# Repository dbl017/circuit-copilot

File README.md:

# CircuitCopilot

Object-aware AI engineering copilot for KiCad combining live design context, engineering documentation, deterministic EE analysis, and safe AI-assisted design workflows.

## Vision

> **CircuitCopilot is an object-aware AI engineering assistant for KiCad that combines live design context, authoritative engineering documentation, deterministic EE tools, and multimodal reasoning to help engineers understand, validate, troubleshoot, learn, and safely modify electronic designs without leaving their EDA workflow.**

The signature interaction CircuitCopilot is working toward:

```
Engineer
  -> hover/select component in KiCad
  -> CircuitCopilot automatically understands the selected object
  -> understands circuit/connectivity context
  -> retrieves authoritative documentation
  -> performs deterministic EE analysis when appropriate
  -> AI explains the result
  -> suggests an engineering action
  -> previews the change
  -> engineer approves
  -> KiCad action occurs
```

The core idea: **AI should understand what the engineer is currently working on without requiring the engineer to manually describe the entire circuit to a chatbot.**

This vision is a working hypothesis and is expected to evolve as the project is built and learned from.

## Why This Project?

General-purpose chatbots can already answer electronics questions, but they have no direct awareness of the object currently selected in an EDA tool, the design's connectivity, the project's state, component relationships, or the engineer's workflow context. CircuitCopilot explores what changes when AI is brought directly into the engineering workflow itself, instead of living in a separate chat window that has to be told everything by hand.

## Core Principles

- Object-aware: understand the design and the selected object, not just free text.
- Evidence-backed: engineering answers should cite authoritative sources.
- Engineering validation: deterministic calculations where practical, not just LLM reasoning.
- Human-in-the-loop: the engineer approves consequential design changes.
- Incremental: build and learn one capability at a time.
- Learning-oriented: understanding the system matters as much as the system working.

See [`docs/architecture/overview.md`](docs/architecture/overview.md) for the full philosophy and architectural categories.

## Current Status

**M0 — Foundations.**

This project is in very early development. No application functionality exists yet: there is no KiCad connection, no agents, no RAG, and no UI. The repository currently contains project structure, documentation, and a roadmap only. See [`progress/CURRENT.md`](progress/CURRENT.md) for the active sprint.

## Proposed Architecture

CircuitCopilot is currently exploring a multi-agent architecture (Orchestrator, Design Agent, Documentation Agent, EE Analysis Agent, Vision Agent, Tutor Agent, Component/Library Agent). **This is provisional and subject to change** — see [`docs/architecture/overview.md`](docs/architecture/overview.md) for details, and note that fewer agents, or a single agent with deterministic tools, may turn out to be the better design. That comparison is itself a planned milestone (M6).

## Roadmap

See [`ROADMAP.md`](ROADMAP.md) for the full milestone plan, from M0 (Foundations) through M10 (Advanced / Innovation Sandbox).

## Learning Project

CircuitCopilot is both an engineering project and a structured learning project. It is being built progressively, on purpose, to learn: EDA automation, KiCad APIs, Python software engineering, Git/GitHub practices, AI/RAG, agent design, multimodal AI, and engineering validation. AI coding assistants are used as pair programmers, reviewers, and instructors — not as a way to generate the whole application at once. See [`CONTRIBUTING.md`](CONTRIBUTING.md) for the AI assistant policy and [`docs/learning-log/`](docs/learning-log/README.md) for what's been learned along the way.

## Repository Structure

```
circuit-copilot/
├── README.md, ROADMAP.md, CONTRIBUTING.md, LICENSE
├── docs/            architecture, decision records, research notes, learning log
├── progress/        current sprint, milestone tracking, idea backlog
├── src/circuitcopilot/   kicad/, agents/, knowledge/, engineering/, vision/, ui/
├── tests/           engineering/, retrieval/, agents/
├── examples/        small runnable examples
├── sample-projects/ sample KiCad projects used for development
└── data/            manifests and small permitted sample data (see data/README.md)
```

## Safety / Engineering Disclaimer

CircuitCopilot is experimental engineering software and should not be relied upon for safety-critical design decisions without independent professional verification.

## License

[MIT](LICENSE)

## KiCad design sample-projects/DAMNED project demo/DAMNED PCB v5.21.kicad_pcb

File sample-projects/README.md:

# Sample Projects

This directory contains KiCad projects used to develop and evaluate CircuitCopilot.

## DAMNED

`DAMNED project demo/` is an existing, working embedded-electronics KiCad project being used as the first realistic CircuitCopilot test fixture. It predates CircuitCopilot and has been opened across more than one KiCad version, so its schematic and PCB files may report different KiCad generator versions from each other and from the currently installed KiCad release — that's expected, and is not something to "fix" by hand.

It will eventually help test:

- KiCad IPC connectivity
- board/component enumeration
- net/connectivity analysis
- component-context extraction
- engineering checks
- documentation retrieval
- object-aware assistance

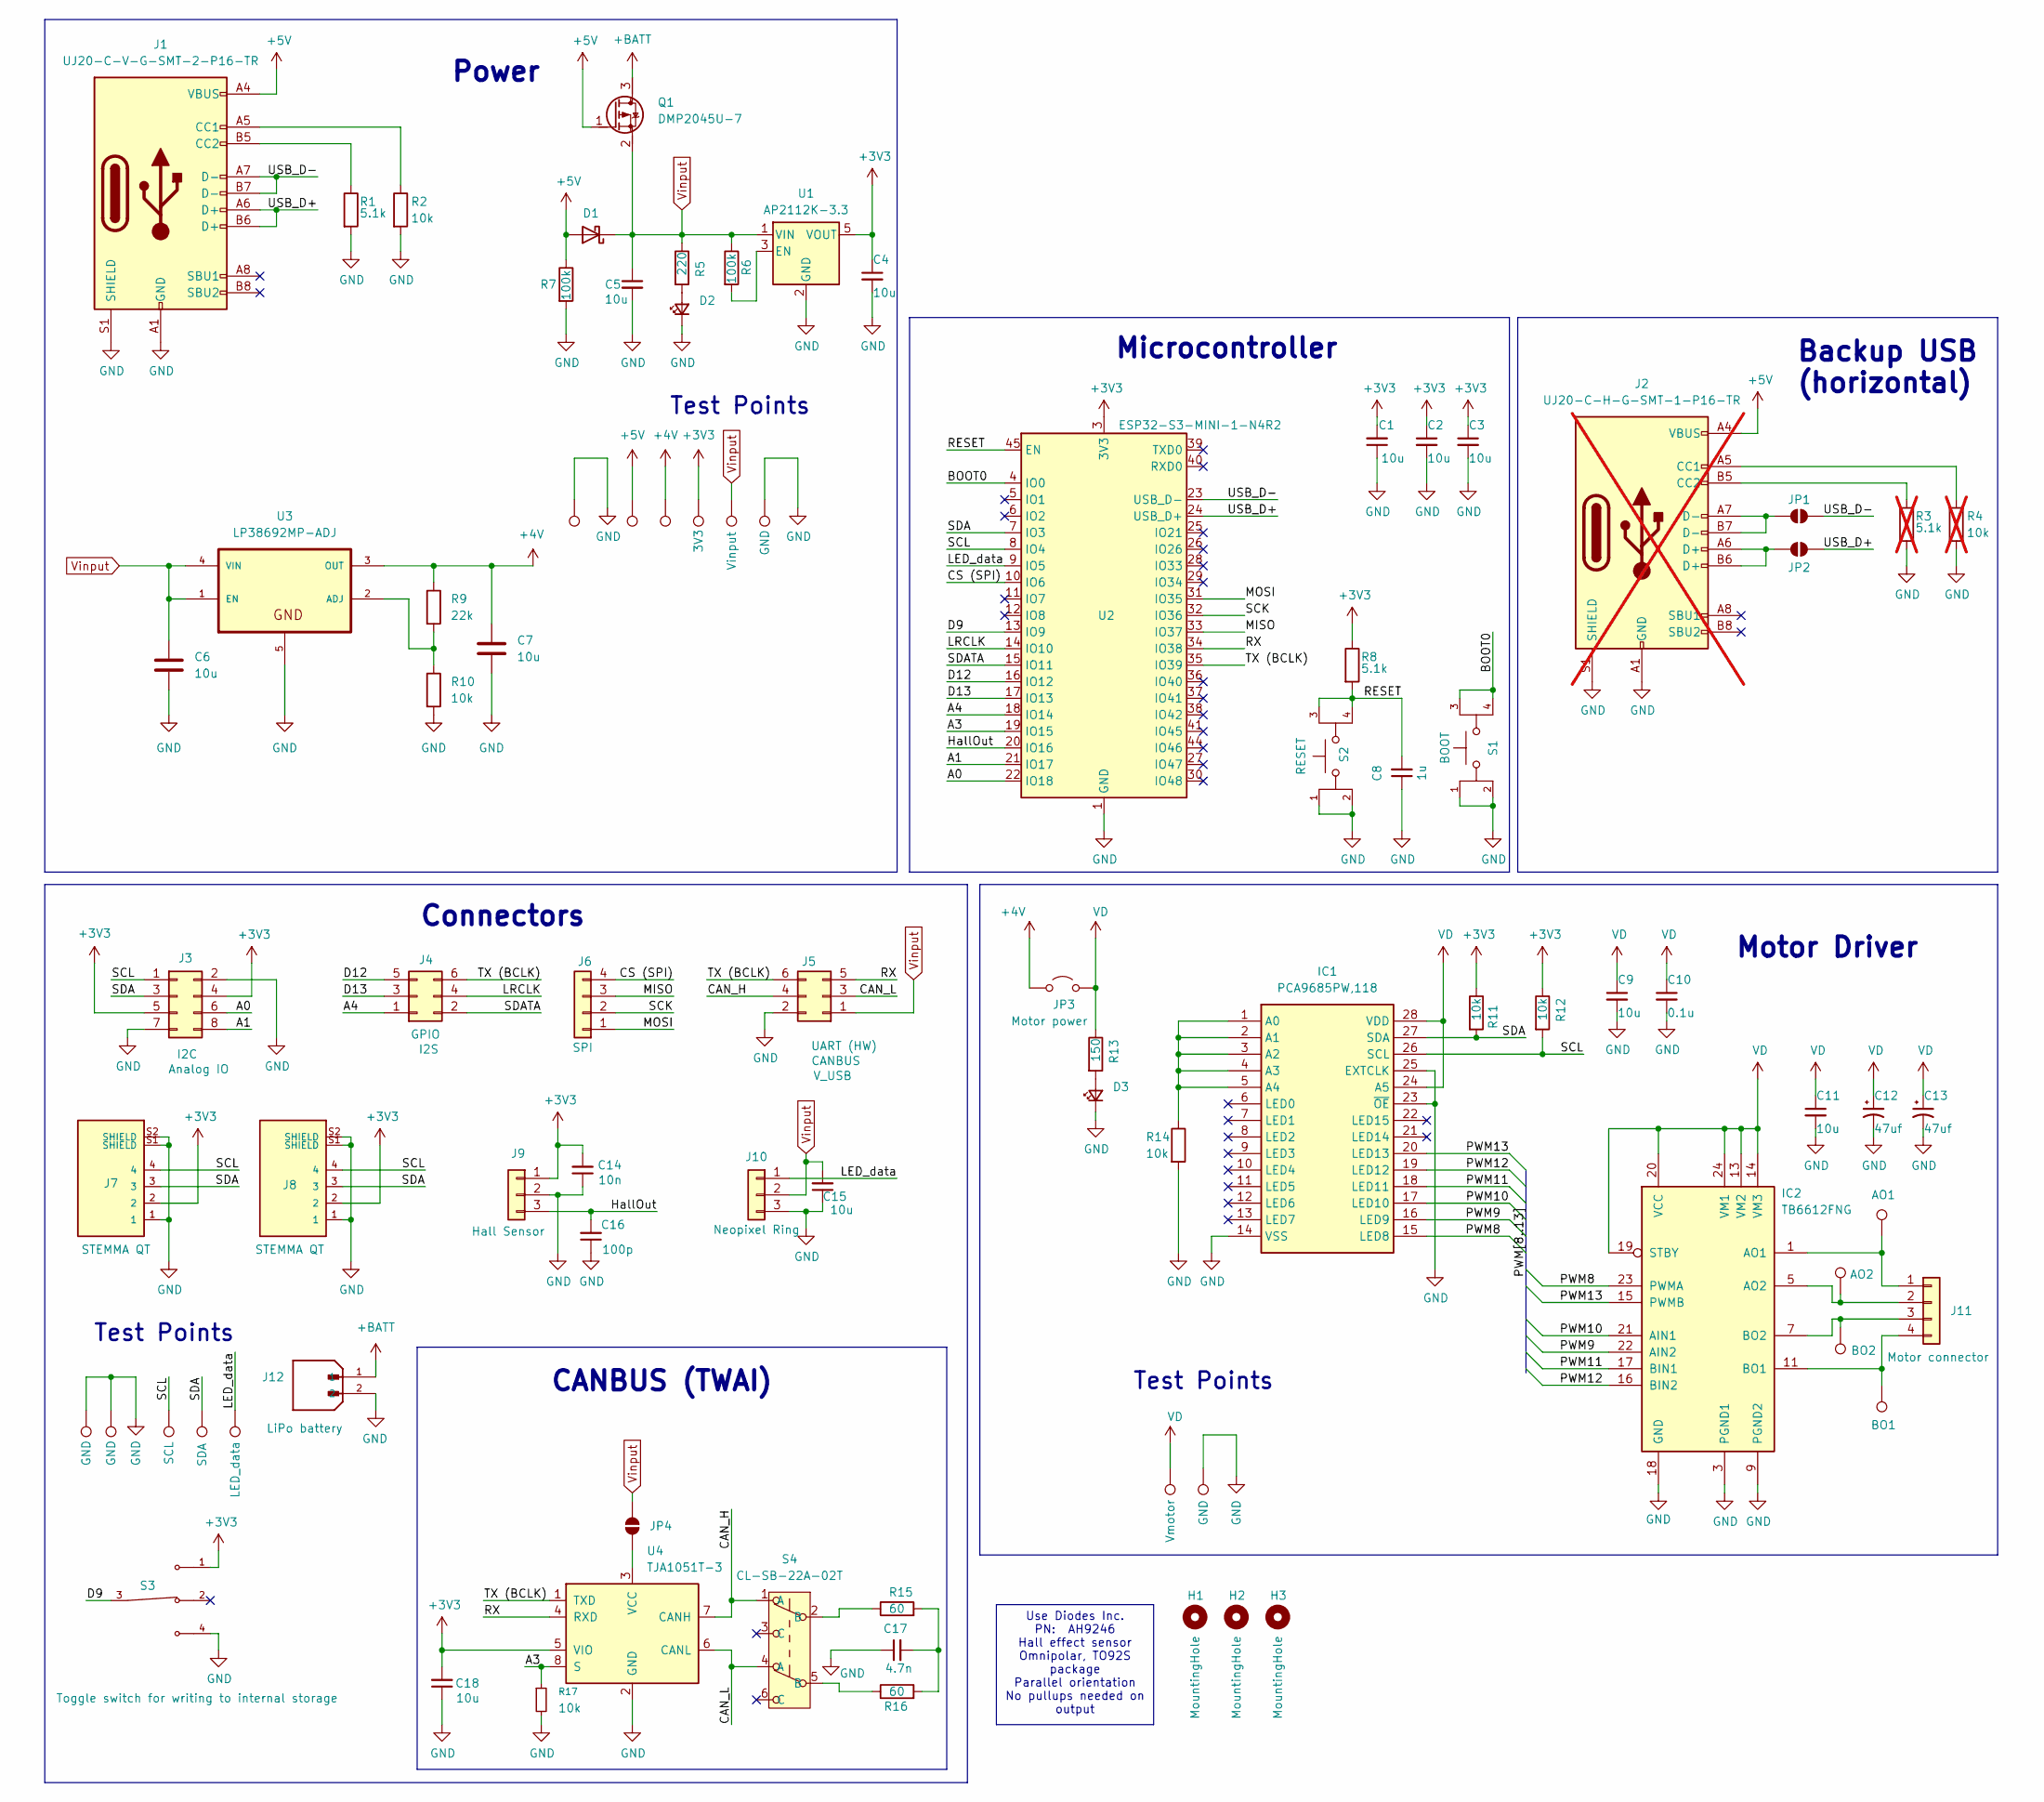
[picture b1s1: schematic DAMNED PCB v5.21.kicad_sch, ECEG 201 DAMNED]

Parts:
C1, C2, C3, C4, C5, C6, C7, C9, C11, C15, C18: 10u; C_0805_2012Metric
C8: 1u; C_0805_2012Metric
C10: 0.1u; C_0805_2012Metric
C12, C13: 47uf; CP_Elec_5x5.3
C14: 10n; C_0805_2012Metric
C16: 100p; C_0805_2012Metric
C17: 4.7n; C_0805_2012Metric
D1: SDT5A50SAF-13; Manufacturer_Part_Number SDT5A50SAF-13; Mouser Part Number 621-SDT5A50SAF-13
D2: LS T676-Q1R2-1; LS_T676
D3: LG T676-P1Q2-24; LS_T676
H1, H2, H3: MountingHole; MountingHole_3mm_Pad
IC1: PCA9685PW,118; SOP65P640X110-28N; Manufacturer_Part_Number PCA9685PW,118; Mouser Part Number 771-PCA9685PW,118
IC2: TB6612FNG; SSOP-24_5.3x8.2mm_P0.65mm
J1: UJ20-C-V-G-SMT-2-P16-TR
J2: UJ20-C-H-G-SMT-1-P16-TR; JAE_DX07S016JA1R1500; not fitted
J3: Conn_02x04_Odd_Even; PinSocket_2x04_P2.54mm_Vertical
J4, J5: Conn_02x03_Odd_Even; PinSocket_2x03_P2.54mm_Vertical
J6: PPPC041LGBN-RC; PinSocket_1x04_P2.54mm_Vertical; Manufacturer_Part_Number PPPC041LGBN-RC
J7, J8: BM04B-SRSS-TB
J9: SLM-103-01-G-S; PinSocket_1x03_P2.54mm_Vertical; PARTREV E
J10: SLW-103-01-T-S
J11: B4B-PH-K-S; Manufacturer_Part_Number B4B-PH-K-S(LF)(SN)
J12: B2B-PH-SM4-TB; PARTREV N/A
JP1, JP2, JP4: SolderJumper_2_Open; SolderJumper-2_P1.3mm_Open_TrianglePad1.0x1.5mm
JP3: PREC002SAAN-RC; PinHeader_1x02_P2.54mm_Vertical
Q1: DMP2045U-7; SOT96P240X115-3N; Manufacturer_Part_Number DMP2045U-7; Mouser Part Number 621-DMP2045U-7
R1, R8: 5.1k; R_0805_2012Metric
R2, R10, R11, R12, R14, R17: 10k; R_0805_2012Metric
R3: 5.1k; R_0805_2012Metric; not fitted
R4: 10k; R_0805_2012Metric; not fitted
R5: 220; R_0805_2012Metric
R6, R7: 100k; R_0805_2012Metric
R9: 22k; R_0805_2012Metric
R13: 150; R_0805_2012Metric
R15, R16: 60; R_0805_2012Metric
S1, S2: TL3365AF180QG; SW_TL3365AF180QG; PARTREV A
S3: CL-SB-13B-01T; SW_CL-SB-13B-01T; PARTREV N/A
S4: CL-SB-22A-02T; Manufacturer_Part_Number EG1390B; Mouser Part Number 612-EG1390B
TP1, TP2, TP3, TP5, TP6, TP11, TP12, TP13, TP14, TP15, TP16, TP17: RCWCTE; TP420X150
TP4: TestPoint_Pad_D1.0mm
TP7, TP8, TP9, TP10: TestPoint_Pad_D2.0mm
U1: AP2112K-3.3; SOT-23-5
U2: ESP32-S3-MINI-1-N4R2; ESP32-S3-MINI-1-N8
U3: LP38692MP-ADJ; SOT223-5
U4: TJA1051T-3; SOIC-8_3.9x4.9mm_P1.27mm

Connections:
+3V3: C1.2, C2.1, C3.1, C4.1, C14.2, C18.2, J3.4, J3.5, J7.2, J8.2, J9.1, R8.1, R11.1, R12.1, S3.1, TP3.1, U1.5 (VOUT), U2.3 (3V3), U4.5 (VIO)
+4V: C7.1, JP3.1 (A), R9.1, TP2.1, U3.3 (OUT)
+5V: D1.2 (A), J1.A4 (VBUS), J1.A9 (VBUS), J1.B4 (VBUS), J1.B9 (VBUS), J2.A4 (VBUS), J2.A9 (VBUS), J2.B4 (VBUS), J2.B9 (VBUS), Q1.1 (G), R7.1, TP1.1
+BATT: J12.1, Q1.3 (D)
/A0: J3.6, U2.22 (IO18)
/A1: J3.8, U2.21 (IO17)
/A3: R17.1, U2.19 (IO15), U4.8 (S)
/A4: J4.1, U2.18 (IO14)
/BOOT0: S1.3, S1.4, U2.4 (IO0)
/CAN_H: J5.4, S4.1 (A), U4.7 (CANH)
/CAN_L: J5.3, S4.4 (A), U4.6 (CANL)
/CS (SPI): J6.4, U2.10 (IO6)
/D9: S3.3, U2.13 (IO9)
/D12: J4.5, U2.16 (IO12)
/D13: J4.3, U2.17 (IO13)
/HallOut: C16.2, J9.3, U2.20 (IO16)
/LED_data: J10.1, TP15.1, U2.9 (IO5)
/LRCLK: J4.4, U2.14 (IO10)
/MISO: J6.3, U2.33 (IO37)
/MOSI: J6.1, U2.31 (IO35)
/PWM8: IC1.15 (LED8), IC2.23 (PWMA)
/PWM9: IC1.16 (LED9), IC2.22 (AIN2)
/PWM10: IC1.17 (LED10), IC2.21 (AIN1)
/PWM11: IC1.18 (LED11), IC2.17 (BIN1)
/PWM12: IC1.19 (LED12), IC2.16 (BIN2)
/PWM13: IC1.20 (LED13), IC2.15 (PWMB)
/RESET: C8.2, R8.2, S2.3, S2.4, U2.45 (EN)
/RX: J5.5, U2.34 (IO38), U4.4 (RXD)
/SCK: J6.2, U2.32 (IO36)
/SCL: IC1.26 (SCL), J3.1, J7.4, J8.4, R12.2, TP13.1, U2.8 (IO4)
/SDA: IC1.27 (SDA), J3.3, J7.3, J8.3, R11.2, TP14.1, U2.7 (IO3)
/SDATA: J4.2, U2.15 (IO11)
/TX (BCLK): J4.6, J5.6, U2.35 (IO39), U4.1 (TXD)
/USB_D+: J1.A6 (D+), J1.B6 (D+), JP2.1 (A), U2.24 (USB_D+)
/USB_D-: J1.A7 (D-), J1.B7 (D-), JP1.1 (A), U2.23 (USB_D-)
GND: C1.1, C2.2, C3.2, C4.2, C5.2, C6.2, C7.2, C8.1, C9.2, C10.2, C11.2, C12.2, C13.2, C14.1, C15.1, C16.1, C17.1, C18.1, D2.1 (K), D3.1 (K), IC1.14 (VSS), IC1.23 (~OE), IC1.25 (EXTCLK), IC2.3 (PGND1), IC2.4 (PGND1), IC2.9 (PGND2), IC2.10 (PGND2), IC2.18 (GND), J1.A1 (GND), J1.A12 (GND), J1.B1 (GND), J1.B12 (GND), J1.S1 (SHIELD), J2.A1 (GND), J2.A12 (GND), J2.B1 (GND), J2.B12 (GND), J2.S1 (SHIELD), J3.2, J3.7, J5.2, J7.1, J7.S1 (SHIELD), J7.S2 (SHIELD), J8.1, J8.S1 (SHIELD), J8.S2 (SHIELD), J9.2, J10.3, J12.2, R1.2, R2.2, R3.2, R4.2, R7.2, R10.2, R14.2, R17.2, S1.1, S1.2, S2.1, S2.2, S3.4, TP5.1, TP6.1, TP11.1, TP12.1, TP17.1, U1.2 (GND), U2.1 (GND), U2.2 (GND), U2.42 (GND), U2.43 (GND), U2.46 (GND), U2.47 (GND), U2.48 (GND), U2.49 (GND), U2.50 (GND), U2.51 (GND), U2.52 (GND), U2.53 (GND), U2.54 (GND), U2.55 (GND), U2.56 (GND), U2.57 (GND), U2.58 (GND), U2.59 (GND), U2.60 (GND), U2.61 (GND), U2.61_1 (GND), U2.61_2 (GND), U2.61_3 (GND), U2.61_4 (GND), U2.61_5 (GND), U2.61_6 (GND), U2.61_7 (GND), U2.61_8 (GND), U2.62 (GND), U2.63 (GND), U2.64 (GND), U2.65 (GND), U3.5, U4.2 (GND)
unnamed: C17.2, R15.2, R16.2
unnamed: D2.2 (A), R5.2
unnamed: D3.2 (A), R13.2
unnamed: IC1.1 (A0), IC1.2 (A1), IC1.3 (A2), IC1.4 (A3), IC1.5 (A4), R14.1
unnamed: J1.A5 (CC1), R2.1
unnamed: J1.B5 (CC2), R1.1
unnamed: J2.A5 (CC1), R4.1
unnamed: J2.B5 (CC2), R3.1
unnamed: IC2.1 (AO1), IC2.2 (AO1), J11.1, TP7.1
unnamed: IC2.5 (AO2), IC2.6 (AO2), J11.2, TP8.1
unnamed: IC2.7 (BO2), IC2.8 (BO2), J11.3, TP9.1
unnamed: IC2.11 (BO1), IC2.12 (BO1), J11.4, TP10.1
unnamed: J2.A7 (D-), J2.B7 (D-), JP1.2 (B)
unnamed: J2.A6 (D+), J2.B6 (D+), JP2.2 (B)
unnamed: JP4.1 (A), U4.3 (VCC)
unnamed: R15.1, S4.2 (B)
unnamed: R16.1, S4.5 (B)
unnamed: R6.2, U1.3 (EN)
unnamed: R9.2, R10.1, U3.2 (ADJ)
VD: C9.1, C10.1, C11.1, C12.1, C13.1, IC1.24 (A5), IC1.28 (VDD), IC2.13 (VM2), IC2.14 (VM3), IC2.19 (STBY), IC2.20 (VCC), IC2.24 (VM1), JP3.2 (B), R13.1, TP16.1
Vinput: C5.1, C6.1, C15.2, D1.1 (K), J5.1, J10.2, JP4.2 (B), Q1.2 (S), R5.1, R6.1, TP4.1, U1.1 (VIN), U3.1 (EN), U3.4 (VIN)

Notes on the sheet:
Test Points
Connectors
Backup USB (horizontal)
Microcontroller
CANBUS (TWAI)
Power
Motor Driver
Use Diodes Inc. PN: AH9246 Hall effect sensor Omnipolar, TO92S package Parallel orientation No pullups needed on output

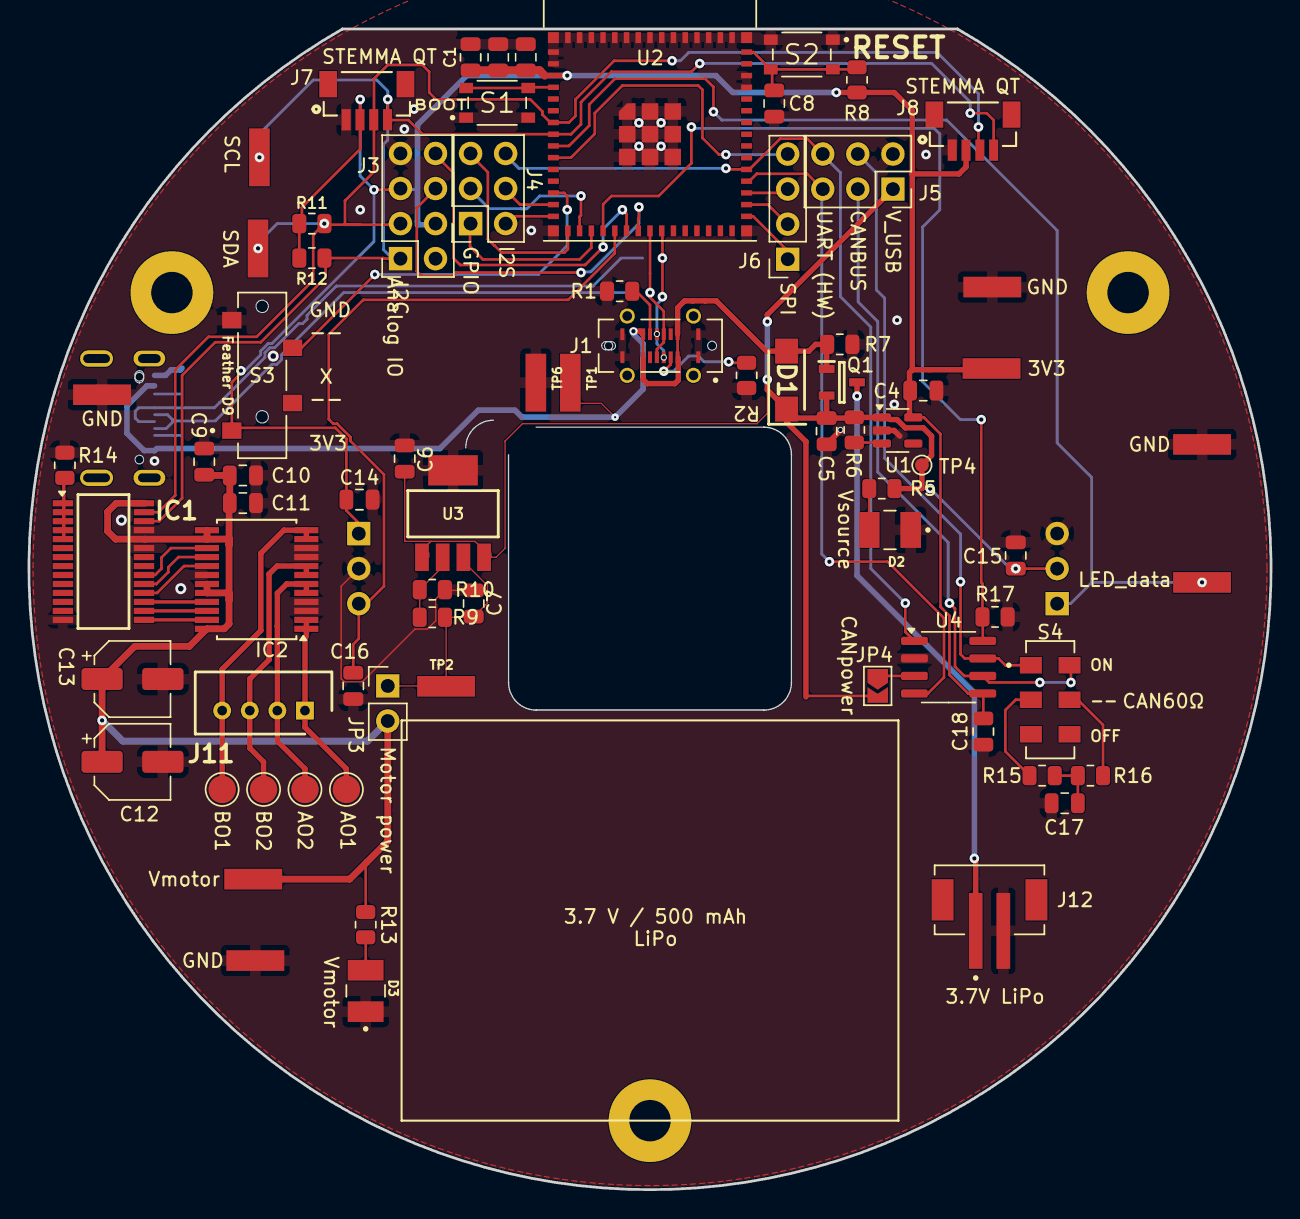
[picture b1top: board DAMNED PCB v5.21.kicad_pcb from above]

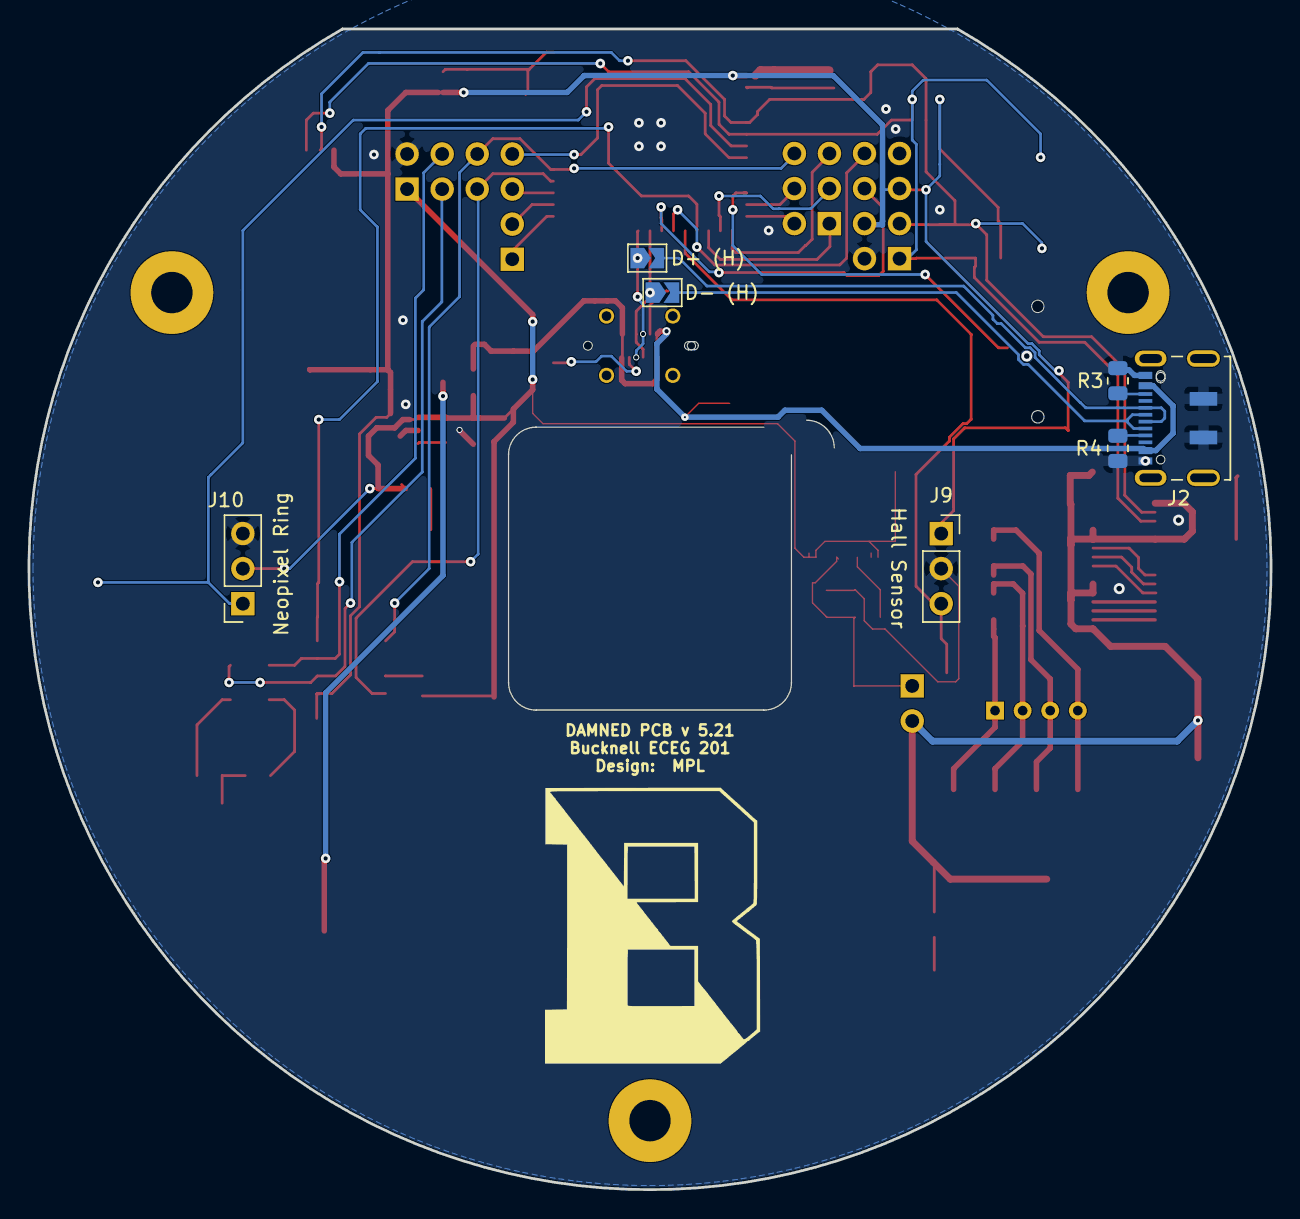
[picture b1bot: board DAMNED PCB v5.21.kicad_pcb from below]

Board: 2 copper layers, 90.0 x 84.1 mm, 85 parts (7 on the bottom side), 57 nets.
